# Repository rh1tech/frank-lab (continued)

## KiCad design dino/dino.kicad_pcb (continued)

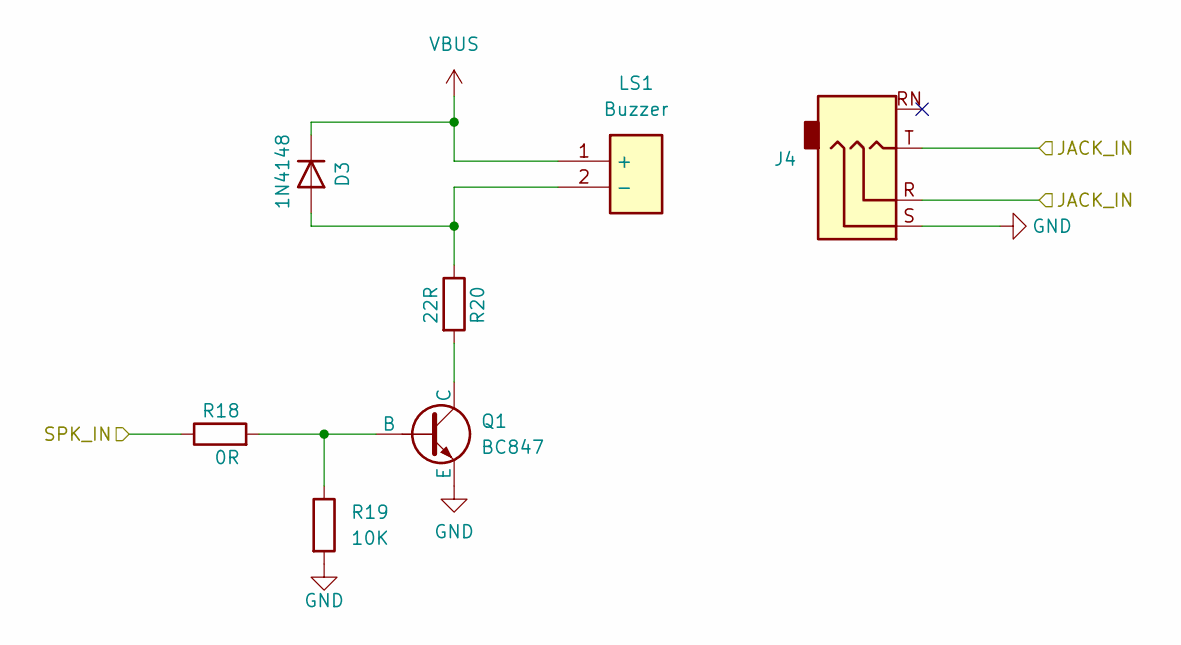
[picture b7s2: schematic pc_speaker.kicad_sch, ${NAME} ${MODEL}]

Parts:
D3: 1N4148; D_SOD-323
J4: PJ-320D; AudioJack_3.5mm_PJ320D_AudioOut
LS1: Buzzer; Buzzer_12x8.5RM6.5; Mouser Part Number 490-CMT-7525-80SMTTR
Q1: BC847; SOT-23
R18: 0R; R_0603_1608Metric
R19: 10K; R_0603_1608Metric
R20: 22R; R_0603_1608Metric

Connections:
/JACK_IN: J4.R, J4.T; also elsewhere on the board
/SPK_IN: R18.1; also elsewhere on the board
GND: J4.S, Q1.3 (E), R19.2; also elsewhere on the board
unnamed: D3.2 (A), LS1.2 (-), R20.1
unnamed: Q1.2 (B), R18.2, R19.1
unnamed: Q1.1 (C), R20.2
VBUS: D3.1 (K), LS1.1 (+); also elsewhere on the board

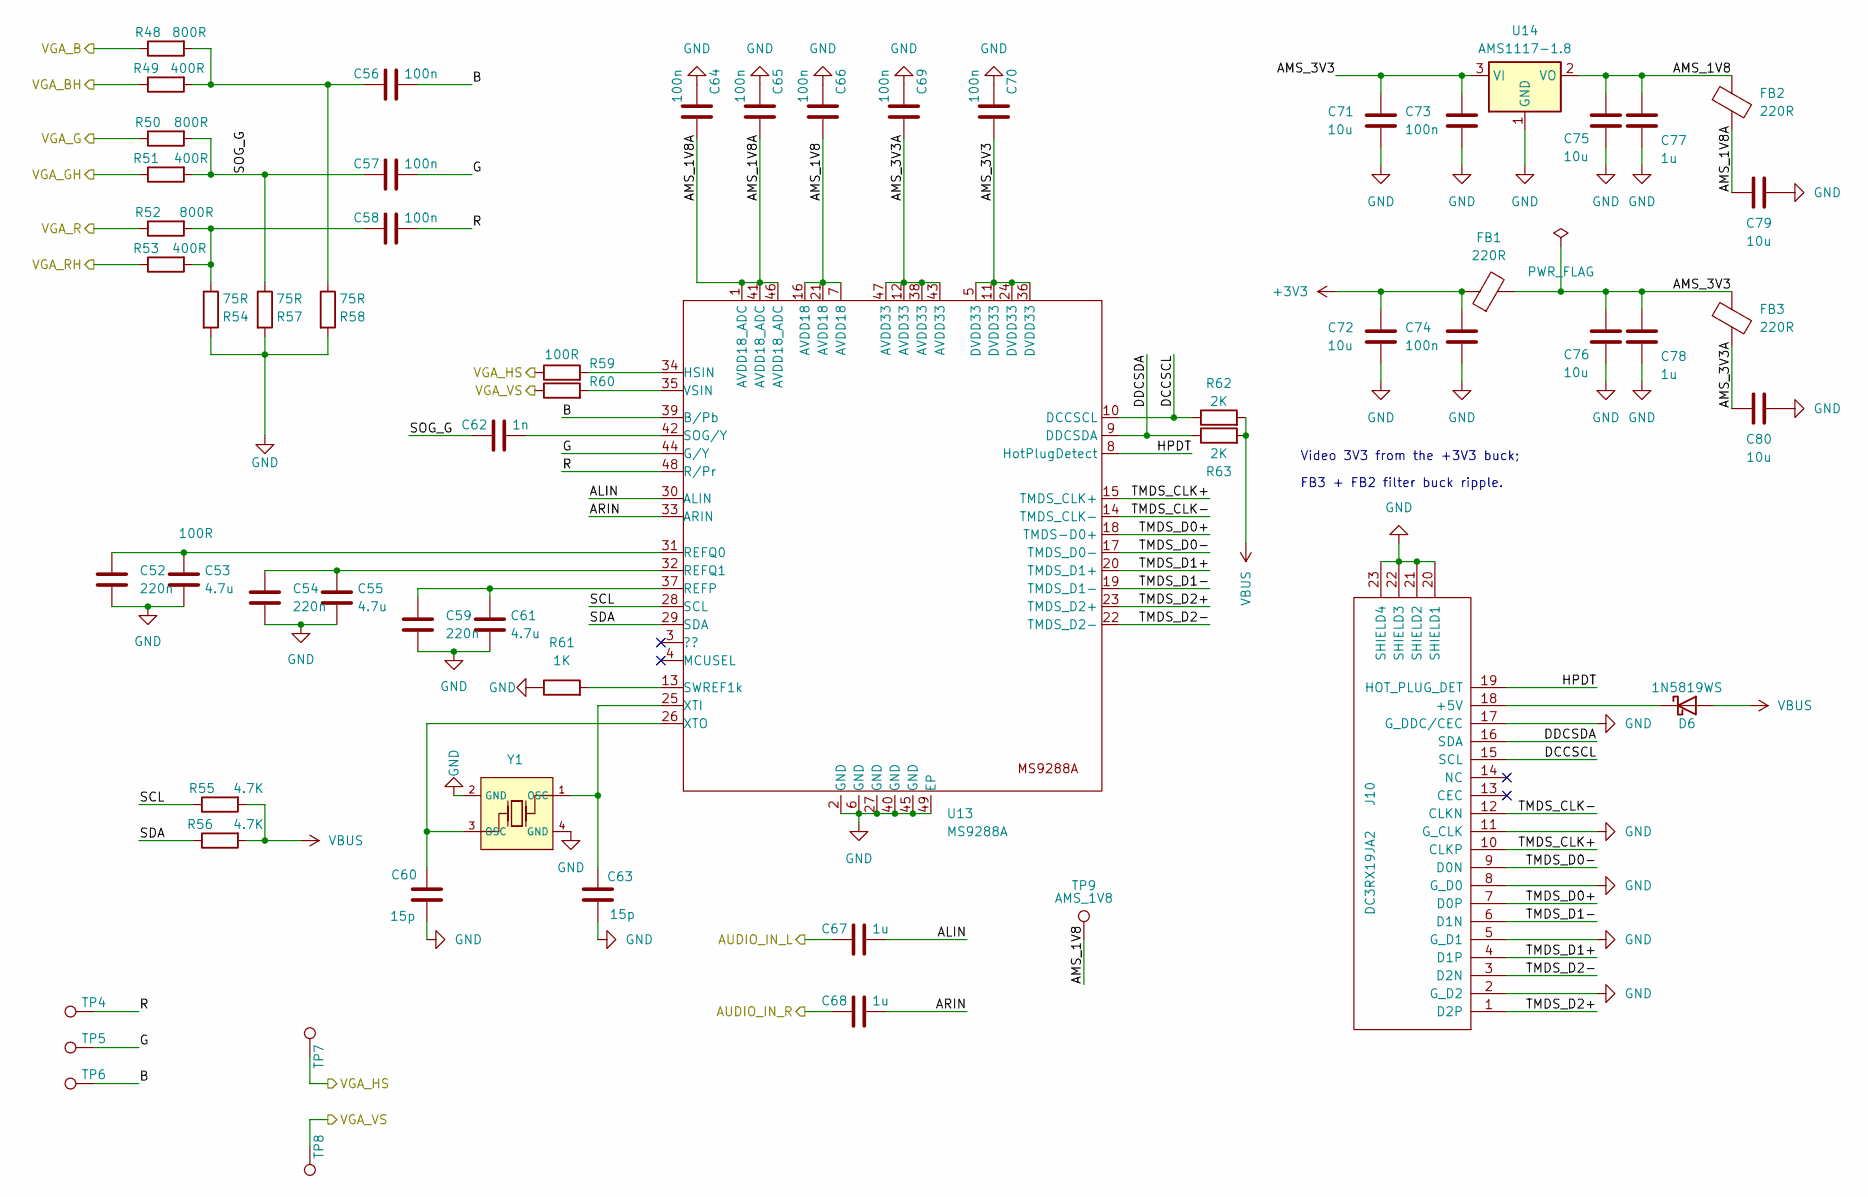
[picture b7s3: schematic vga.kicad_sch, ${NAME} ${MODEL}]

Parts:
C52, C54, C59: 220n; C_0603_1608Metric
C53, C55, C61: 4.7u; C_0603_1608Metric
C56, C57, C58, C64, C65, C66, C69, C70, C73, C74: 100n; C_0603_1608Metric
C60, C63: 15p; C_0603_1608Metric
C62: 1n; C_0603_1608Metric
C67, C68, C77, C78: 1u; C_0603_1608Metric
C71, C72, C75, C76, C79, C80: 10u; C_0603_1608Metric
D6: 1N5819WS; D_SOD-323
FB1, FB2, FB3: 220R; L_0805_2012Metric
J10: DC3RX19JA2; HDMI_Female
R48, R50, R52: 800R; R_0603_1608Metric
R49, R51, R53: 400R; R_0603_1608Metric
R54, R57, R58: 75R; R_0603_1608Metric
R55, R56: 4.7K; R_0603_1608Metric
R59, R60: 100R; R_0603_1608Metric
R61: 1K; R_0603_1608Metric
R62, R63: 2K; R_0603_1608Metric
TP4: R; TestPoint_Pad_1.0x1.0mm
TP5: G; TestPoint_Pad_1.0x1.0mm
TP6: B; TestPoint_Pad_1.0x1.0mm
TP7: HS; TestPoint_Pad_1.0x1.0mm
TP8: VS; TestPoint_Pad_1.0x1.0mm
TP9: AMS_1V8; TestPoint_Pad_1.0x1.0mm
U13: MS9288A; QFN-48_7x7mm_P0.4mm
U14: AMS1117-1.8; SOT-223-3_TabPin2
Y1: 24.576 MHz; Crystal_SMD_2520-4Pin; Frequency Tolerance ±10ppm; Part X322512MSB4SI

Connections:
+3V3: C72.1, C74.1, FB1.1; also elsewhere on the board
/HDMI_AUDIO: C67.2, C68.2; also elsewhere on the board
/RP2350B/GP30: R48.1; also elsewhere on the board
/RP2350B/GP31: R49.1; also elsewhere on the board
/RP2350B/GP32: R50.1; also elsewhere on the board
/RP2350B/GP33: R51.1; also elsewhere on the board
/RP2350B/GP34: R52.1; also elsewhere on the board
/RP2350B/GP35: R53.1; also elsewhere on the board
/RP2350B/GP36: R59.1, TP7.1 (1_1); also elsewhere on the board
/RP2350B/GP37: R60.1, TP8.1 (1_1); also elsewhere on the board
/Video/ALIN: C67.1, U13.30 (ALIN)
/Video/AMS_1V8: C66.1, C75.1, C77.1, FB2.1, TP9.1 (1_1), U13.7 (AVDD18), U13.16 (AVDD18), U13.21 (AVDD18), U14.2 (VO)
/Video/AMS_1V8A: C64.1, C65.1, C79.1, FB2.2, U13.1 (AVDD18_ADC), U13.41 (AVDD18_ADC), U13.46 (AVDD18_ADC)
/Video/AMS_3V3: C70.1, C71.1, C73.1, C76.1, C78.1, FB1.2, FB3.1, U13.5 (DVDD33), U13.11 (DVDD33), U13.24 (DVDD33), U13.36 (DVDD33), U14.3 (VI)
/Video/AMS_3V3A: C69.1, C80.1, FB3.2, U13.12 (AVDD33), U13.38 (AVDD33), U13.43 (AVDD33), U13.47 (AVDD33)
/Video/ARIN: C68.1, U13.33 (ARIN)
/Video/B: C56.1, TP6.1 (1_1), U13.39 (B/Pb)
/Video/DCCSCL: J10.15 (SCL), R62.1, U13.10 (DCCSCL)
/Video/DDCSDA: J10.16 (SDA), R63.1, U13.9 (DDCSDA)
/Video/G: C57.1, TP5.1 (1_1), U13.44 (G/Y)
/Video/HPDT: J10.19 (HOT_PLUG_DET), U13.8 (HotPlugDetect)
/Video/R: C58.1, TP4.1 (1_1), U13.48 (R/Pr)
/Video/SCL: R55.1, U13.28 (SCL)
/Video/SDA: R56.1, U13.29 (SDA)
/Video/SOG_G: C57.2, C62.2, R50.2, R51.2, R57.1
/Video/TMDS_CLK+: J10.10 (CLKP), U13.15 (TMDS_CLK+)
/Video/TMDS_CLK-: J10.12 (CLKN), U13.14 (TMDS_CLK-)
/Video/TMDS_D0+: J10.7 (D0P), U13.18 (TMDS-D0+)
/Video/TMDS_D0-: J10.9 (D0N), U13.17 (TMDS_D0-)
/Video/TMDS_D1+: J10.4 (D1P), U13.20 (TMDS_D1+)
/Video/TMDS_D1-: J10.6 (D1N), U13.19 (TMDS_D1-)
/Video/TMDS_D2+: J10.1 (D2P), U13.23 (TMDS_D2+)
/Video/TMDS_D2-: J10.3 (D2N), U13.22 (TMDS_D2-)
GND: C52.2, C53.2, C54.2, C55.2, C59.2, C60.2, C61.2, C63.2, C64.2, C65.2, C66.2, C69.2, C70.2, C71.2, C72.2, C73.2, C74.2, C75.2, C76.2, C77.2, C78.2, C79.2, C80.2, J10.2 (G_D2), J10.5 (G_D1), J10.8 (G_D0), J10.11 (G_CLK), J10.17 (G_DDC/CEC), J10.20 (SHIELD1), J10.21 (SHIELD2), J10.22 (SHIELD3), J10.23 (SHIELD4), R54.2, R57.2, R58.2, R61.1, U13.2 (GND), U13.6 (GND), U13.27 (GND), U13.40 (GND), U13.45 (GND), U13.49 (EP), U14.1 (GND), Y1.2 (GND), Y1.4 (GND); also elsewhere on the board
unnamed: C56.2, R48.2, R49.2, R58.1
unnamed: C58.2, R52.2, R53.2, R54.1
unnamed: D6.1 (K), J10.18 (+5V)
unnamed: R59.2, U13.34 (HSIN)
unnamed: C59.1, C61.1, U13.37 (REFP)
unnamed: C52.1, C53.1, U13.31 (REFQ0)
unnamed: C54.1, C55.1, U13.32 (REFQ1)
unnamed: C62.1, U13.42 (SOG/Y)
unnamed: R61.2, U13.13 (SWREF1k)
unnamed: R60.2, U13.35 (VSIN)
unnamed: C63.1, U13.25 (XTI), Y1.1 (OSC)
unnamed: C60.1, U13.26 (XTO), Y1.3 (OSC)
VBUS: D6.2 (A), R55.2, R56.2, R62.2, R63.2; also elsewhere on the board

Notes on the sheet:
FB3 + FB2 filter buck ripple.
Video 3V3 from the +3V3 buck;

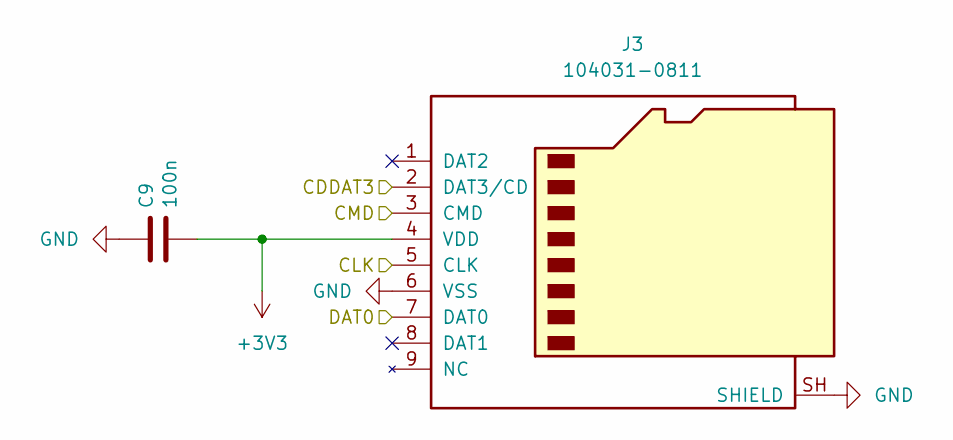
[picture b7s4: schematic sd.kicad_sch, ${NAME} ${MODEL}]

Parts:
C9: 100n; C_0603_1608Metric
J3: 104031-0811; MicroSD_SMD_Long

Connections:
+3V3: C9.2, J3.4 (VDD); also elsewhere on the board
/Micro SD/CDDAT3: J3.2 (DAT3/CD); also elsewhere on the board
/Micro SD/CLK: J3.5 (CLK); also elsewhere on the board
/Micro SD/CMD: J3.3 (CMD); also elsewhere on the board
/Micro SD/DAT0: J3.7 (DAT0); also elsewhere on the board
GND: C9.1, J3.6 (VSS), J3.SH (SHIELD); also elsewhere on the board

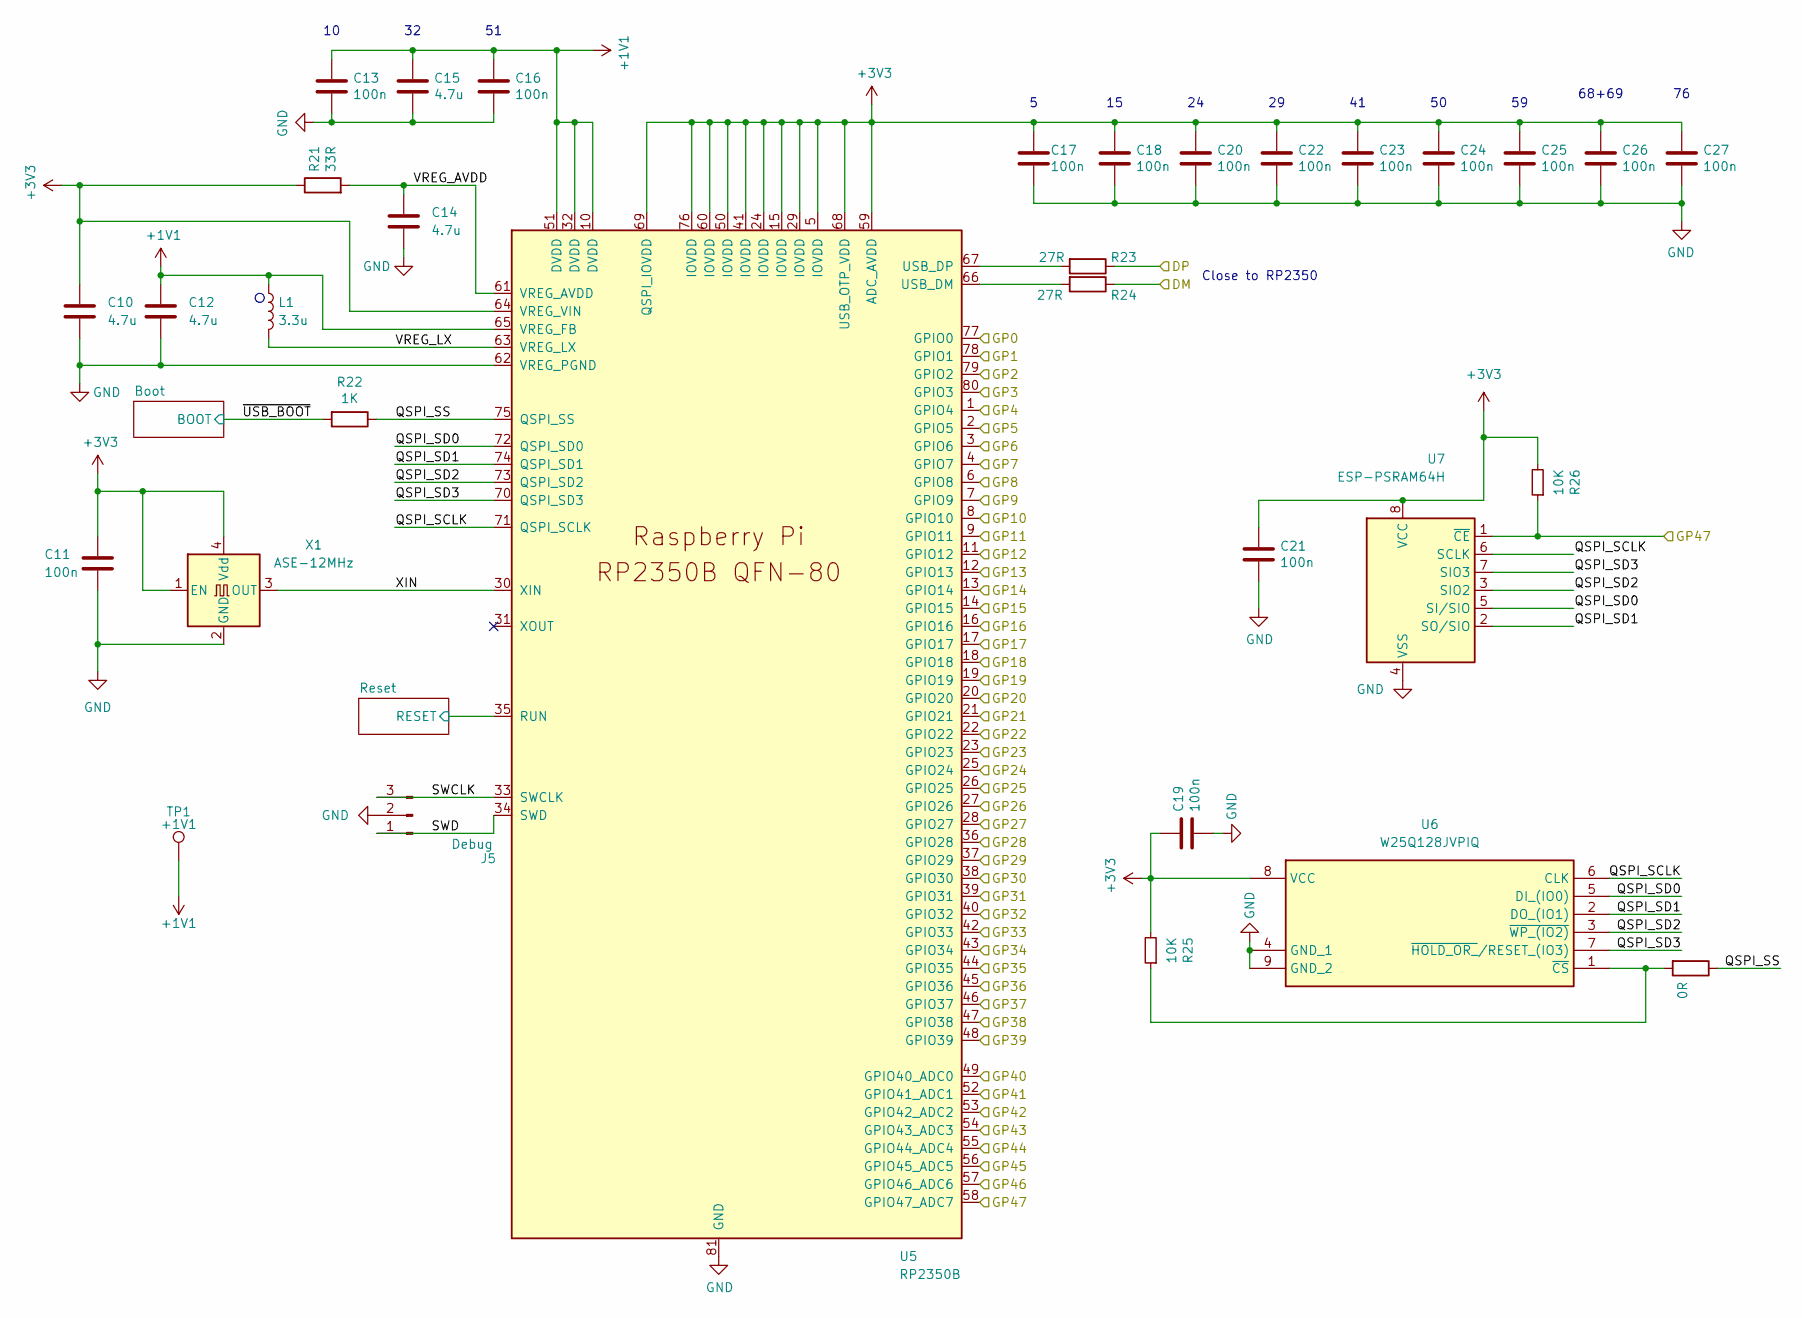
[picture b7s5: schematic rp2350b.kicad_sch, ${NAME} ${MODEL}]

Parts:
C10, C12, C14, C15: 4.7u; C_0603_1608Metric
C11, C13, C16, C17, C18, C19, C20, C21, C22, C23, C24, C25, C26, C27: 100n; C_0603_1608Metric
J5: Debug; JST_SH_1x03_P1.00mm_Vertical
L1: 3.3u; L_LQH2MCN100K02L
R21: 33R; R_0603_1608Metric
R22: 1K; R_0603_1608Metric
R23, R24: 27R; R_0603_1608Metric
R25, R26: 10K; R_0603_1608Metric
R27: 0R; R_0603_1608Metric
TP1: +1V1; TestPoint_Pad_1.0x1.0mm
U5: RP2350B; RP2350-QFN-80_10x10_P0.4mm
U6: W25Q128JVPIQ; SON127P600X500X80-9N-D; Mouser Part Number 454-W25Q128JVPIQ
U7: ESP-PSRAM64H; SO-8
X1: ASE-12MHz; Oscillator_SMD_3225_4Pin

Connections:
+1V1: C12.1, C13.1, C15.1, C16.1, L1.1, TP1.1 (1_1), U5.10 (DVDD), U5.32 (DVDD), U5.51 (DVDD), U5.65 (VREG_FB)
+3V3: C10.1, C11.1, C17.1, C18.1, C19.1, C20.1, C21.1, C22.1, C23.1, C24.1, C25.1, C26.1, C27.1, R21.1, R25.2, R26.2, U5.5 (IOVDD), U5.15 (IOVDD), U5.24 (IOVDD), U5.29 (IOVDD), U5.41 (IOVDD), U5.50 (IOVDD), U5.59 (ADC_AVDD), U5.60 (IOVDD), U5.64 (VREG_VIN), U5.68 (USB_OTP_VDD), U5.69 (QSPI_IOVDD), U5.76 (IOVDD), U6.8 (VCC), U7.8 (VCC), X1.1 (EN), X1.4 (Vdd); also elsewhere on the board
/A0: U5.77 (GPIO0); also elsewhere on the board
/A1: U5.78 (GPIO1); also elsewhere on the board
/A2: U5.79 (GPIO2); also elsewhere on the board
/A3: U5.80 (GPIO3); also elsewhere on the board
/A4: U5.1 (GPIO4); also elsewhere on the board
/A5: U5.2 (GPIO5); also elsewhere on the board
/A6: U5.3 (GPIO6); also elsewhere on the board
/A7: U5.4 (GPIO7); also elsewhere on the board
/A8: U5.6 (GPIO8); also elsewhere on the board
/A9: U5.7 (GPIO9); also elsewhere on the board
/A10: U5.8 (GPIO10); also elsewhere on the board
/A11: U5.9 (GPIO11); also elsewhere on the board
/A12: U5.11 (GPIO12); also elsewhere on the board
/A13: U5.12 (GPIO13); also elsewhere on the board
/A14: U5.13 (GPIO14); also elsewhere on the board
/A15: U5.14 (GPIO15); also elsewhere on the board
/CLK: U5.36 (GPIO28); also elsewhere on the board
/D0: U5.16 (GPIO16); also elsewhere on the board
/D1: U5.17 (GPIO17); also elsewhere on the board
/D2: U5.18 (GPIO18); also elsewhere on the board
/D3: U5.19 (GPIO19); also elsewhere on the board
/D4: U5.20 (GPIO20); also elsewhere on the board
/D5: U5.21 (GPIO21); also elsewhere on the board
/D6: U5.22 (GPIO22); also elsewhere on the board
/D7: U5.23 (GPIO23); also elsewhere on the board
/INT: U5.47 (GPIO38); also elsewhere on the board
/M1: U5.28 (GPIO27); also elsewhere on the board
/MREQ: U5.25 (GPIO24); also elsewhere on the board
/Micro SD/CDDAT3: U5.52 (GPIO41_ADC1); also elsewhere on the board
/Micro SD/CLK: U5.53 (GPIO42_ADC2); also elsewhere on the board
/Micro SD/CMD: U5.54 (GPIO43_ADC3); also elsewhere on the board
/Micro SD/DAT0: U5.49 (GPIO40_ADC0); also elsewhere on the board
/NMI: U5.48 (GPIO39); also elsewhere on the board
/RD: U5.26 (GPIO25); also elsewhere on the board
/RESET: U5.37 (GPIO29); also elsewhere on the board
/RP2350B/DM: R24.1; also elsewhere on the board
/RP2350B/DP: R23.1; also elsewhere on the board
/RP2350B/GP30: U5.38 (GPIO30); also elsewhere on the board
/RP2350B/GP31: U5.39 (GPIO31); also elsewhere on the board
/RP2350B/GP32: U5.40 (GPIO32); also elsewhere on the board
/RP2350B/GP33: U5.42 (GPIO33); also elsewhere on the board
/RP2350B/GP34: U5.43 (GPIO34); also elsewhere on the board
/RP2350B/GP35: U5.44 (GPIO35); also elsewhere on the board
/RP2350B/GP36: U5.45 (GPIO36); also elsewhere on the board
/RP2350B/GP37: U5.46 (GPIO37); also elsewhere on the board
/RP2350B/GP47: R26.1, U5.58 (GPIO47_ADC7), U7.1 (~CE)
/RP2350B/QSPI_SCLK: U5.71 (QSPI_SCLK), U6.6 (CLK), U7.6 (SCLK)
/RP2350B/QSPI_SD0: U5.72 (QSPI_SD0), U6.5 (DI_(IO0)), U7.5 (SI/SIO)
/RP2350B/QSPI_SD1: U5.74 (QSPI_SD1), U6.2 (DO_(IO1)), U7.2 (SO/SIO)
/RP2350B/QSPI_SD2: U5.73 (QSPI_SD2), U6.3 (~WP_(IO2)), U7.3 (SIO2)
/RP2350B/QSPI_SD3: U5.70 (QSPI_SD3), U6.7 (~HOLD_OR_/RESET_(IO3)), U7.7 (SIO3)
/RP2350B/QSPI_SS: R22.1, R27.1, U5.75 (QSPI_SS)
/RP2350B/Reset/RESET: U5.35 (RUN); also elsewhere on the board
/RP2350B/SWCLK: J5.3, U5.33 (SWCLK)
/RP2350B/SWD: J5.1, U5.34 (SWD)
/RP2350B/VREG_AVDD: C14.1, R21.2, U5.61 (VREG_AVDD)
/RP2350B/VREG_LX: L1.2, U5.63 (VREG_LX)
/RP2350B/XIN: U5.30 (XIN), X1.3 (OUT)
/RP2350B/~USB_BOOT: R22.2; also elsewhere on the board
/SPEAKER: U5.57 (GPIO46_ADC6); also elsewhere on the board
/TAPE_UART_RX: U5.56 (GPIO45_ADC5); also elsewhere on the board
/UART0_TX: U5.55 (GPIO44_ADC4); also elsewhere on the board
/WR: U5.27 (GPIO26); also elsewhere on the board
GND: C10.2, C11.2, C12.2, C13.2, C14.2, C15.2, C16.2, C17.2, C18.2, C19.2, C20.2, C21.2, C22.2, C23.2, C24.2, C25.2, C26.2, C27.2, J5.2, U5.62 (VREG_PGND), U5.81 (GND), U6.4 (GND_1), U6.9 (GND_2), U7.4 (VSS), X1.2 (GND); also elsewhere on the board
unnamed: R24.2, U5.66 (USB_DM)
unnamed: R23.2, U5.67 (USB_DP)
unnamed: R25.1, R27.2, U6.1 (~CS)

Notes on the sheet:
Close to RP2350
68+69

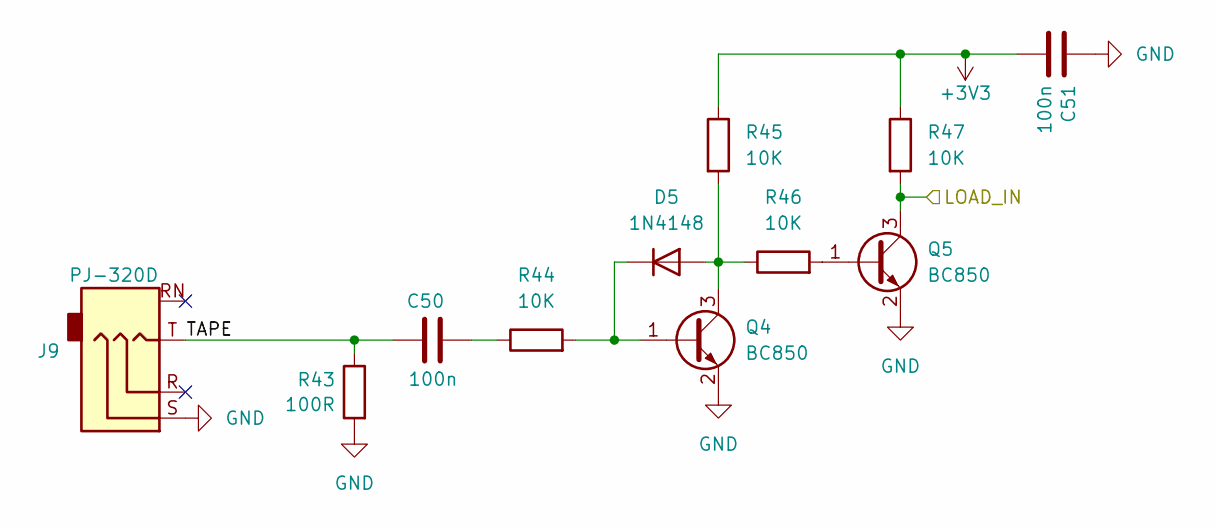
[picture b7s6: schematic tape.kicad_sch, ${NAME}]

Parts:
C50, C51: 100n; C_0603_1608Metric; LCSC C14663
D5: 1N4148; D_SOD-323; LCSC C2128
J9: PJ-320D; AudioJack_3.5mm_PJ320D_TapeIn; LCSC C431535
Q4, Q5: BC850; SOT-23; LCSC C503377
R43: 100R; R_0603_1608Metric; LCSC C22775
R44, R45, R46: 10K; R_0603_1608Metric; LCSC C2906982
R47: 10K; R_0603_1608Metric; LCSC C21190

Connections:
+3V3: C51.2, R45.1, R47.1; also elsewhere on the board
/TAPE_UART_RX: Q5.3 (C), R47.2; also elsewhere on the board
/Tape/TAPE: C50.1, J9.T, R43.1
GND: C51.1, J9.S, Q4.2 (E), Q5.2 (E), R43.2; also elsewhere on the board
unnamed: C50.2, R44.1
unnamed: D5.2 (A), Q4.3 (C), R45.2, R46.1
unnamed: D5.1 (K), Q4.1 (B), R44.2
unnamed: Q5.1 (B), R46.2

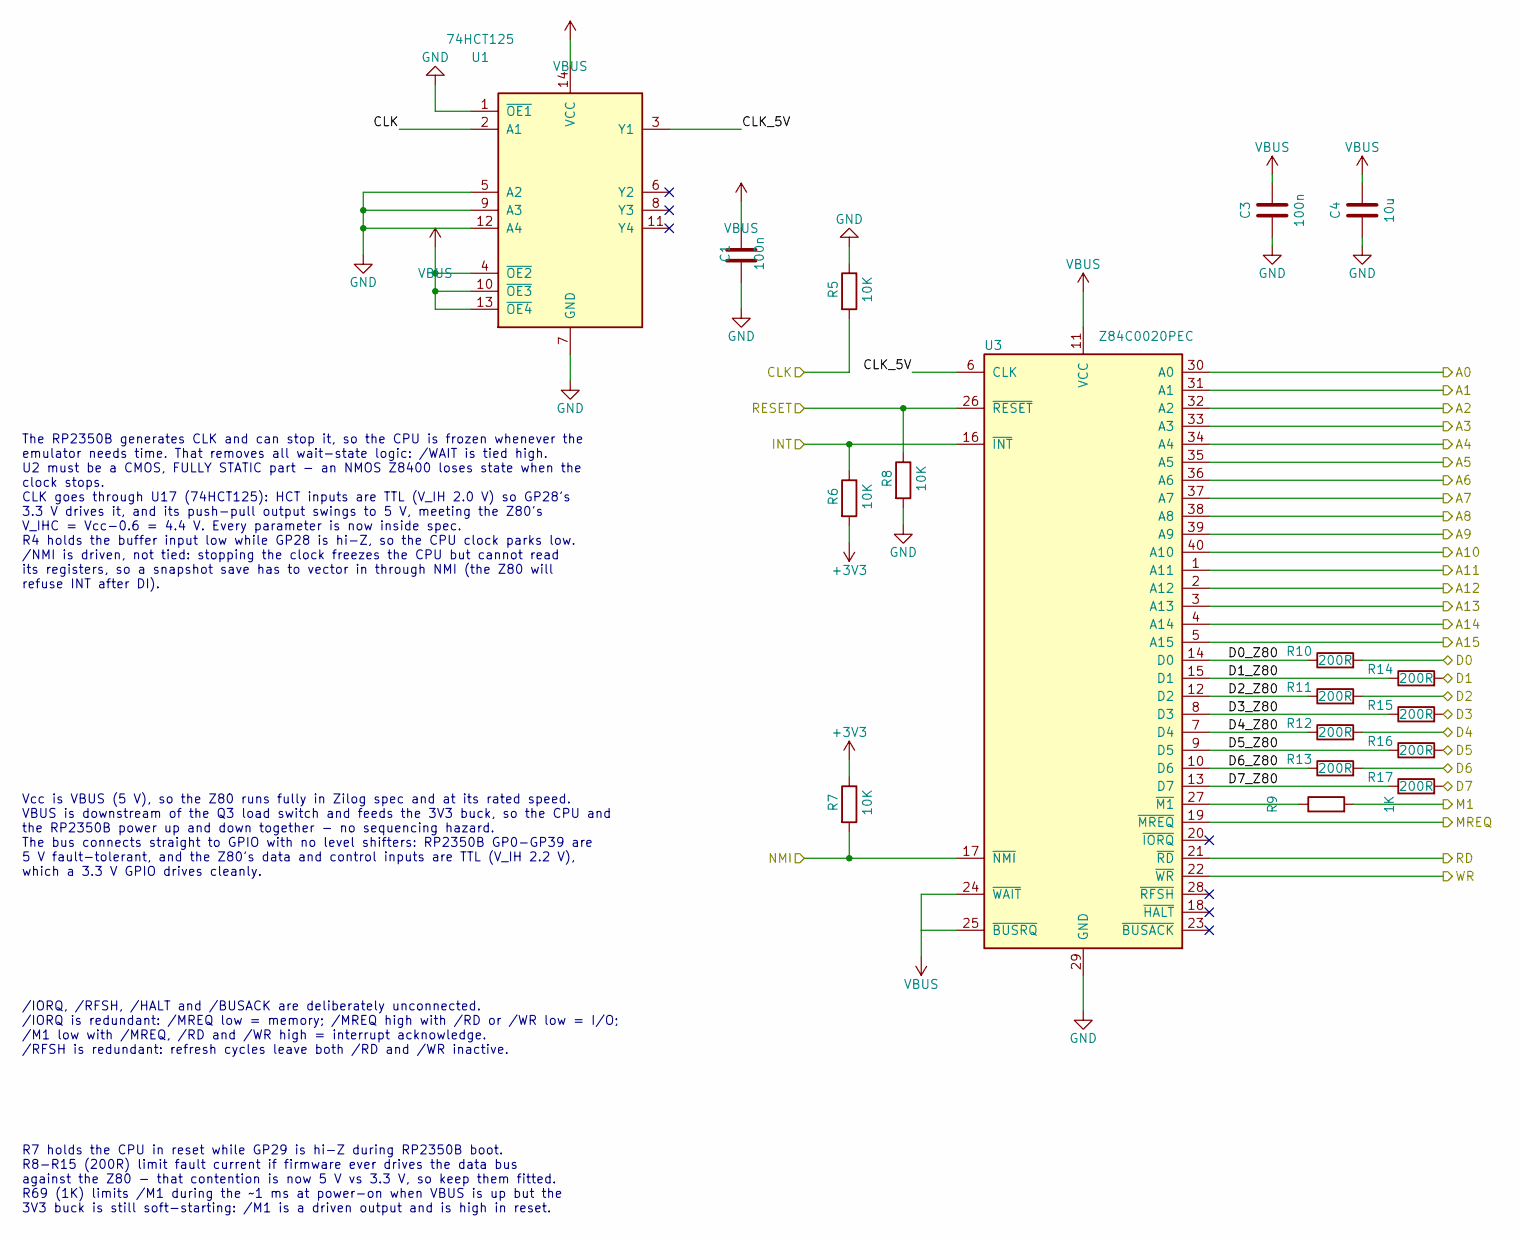
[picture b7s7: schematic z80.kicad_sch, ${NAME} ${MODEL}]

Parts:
C1, C3: 100n; C_0603_1608Metric
C4: 10u; C_0603_1608Metric
R5, R6, R7, R8: 10K; R_0603_1608Metric
R9: 1K; R_0603_1608Metric
R10, R11, R12, R13, R14, R15, R16, R17: 200R; R_0603_1608Metric
U1: 74HCT125; SOIC127P600X175-14N
U3: Z84C0020PEC; DIP-40_W15.24mm_Socket

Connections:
+3V3: R6.2, R7.1; also elsewhere on the board
/A0: U3.30 (A0); also elsewhere on the board
/A1: U3.31 (A1); also elsewhere on the board
/A2: U3.32 (A2); also elsewhere on the board
/A3: U3.33 (A3); also elsewhere on the board
/A4: U3.34 (A4); also elsewhere on the board
/A5: U3.35 (A5); also elsewhere on the board
/A6: U3.36 (A6); also elsewhere on the board
/A7: U3.37 (A7); also elsewhere on the board
/A8: U3.38 (A8); also elsewhere on the board
/A9: U3.39 (A9); also elsewhere on the board
/A10: U3.40 (A10); also elsewhere on the board
/A11: U3.1 (A11); also elsewhere on the board
/A12: U3.2 (A12); also elsewhere on the board
/A13: U3.3 (A13); also elsewhere on the board
/A14: U3.4 (A14); also elsewhere on the board
/A15: U3.5 (A15); also elsewhere on the board
/CLK: R5.2, U1.2 (A1); also elsewhere on the board
/D0: R10.2; also elsewhere on the board
/D1: R14.2; also elsewhere on the board
/D2: R11.2; also elsewhere on the board
/D3: R15.2; also elsewhere on the board
/D4: R12.2; also elsewhere on the board
/D5: R16.2; also elsewhere on the board
/D6: R13.2; also elsewhere on the board
/D7: R17.2; also elsewhere on the board
/INT: R6.1, U3.16 (~INT); also elsewhere on the board
/M1: R9.2; also elsewhere on the board
/MREQ: U3.19 (~MREQ); also elsewhere on the board
/NMI: R7.2, U3.17 (~NMI); also elsewhere on the board
/RD: U3.21 (~RD); also elsewhere on the board
/RESET: R8.1, U3.26 (~RESET); also elsewhere on the board
/WR: U3.22 (~WR); also elsewhere on the board
/Z80/CLK_5V: U1.3 (Y1), U3.6 (CLK)
/Z80/D0_Z80: R10.1, U3.14 (D0)
/Z80/D1_Z80: R14.1, U3.15 (D1)
/Z80/D2_Z80: R11.1, U3.12 (D2)
/Z80/D3_Z80: R15.1, U3.8 (D3)
/Z80/D4_Z80: R12.1, U3.7 (D4)
/Z80/D5_Z80: R16.1, U3.9 (D5)
/Z80/D6_Z80: R13.1, U3.10 (D6)
/Z80/D7_Z80: R17.1, U3.13 (D7)
GND: C1.2, C3.2, C4.2, R5.1, R8.2, U1.1 (~OE1), U1.5 (A2), U1.7 (GND), U1.9 (A3), U1.12 (A4), U3.29 (GND); also elsewhere on the board
unnamed: R9.1, U3.27 (~M1)
VBUS: C1.1, C3.1, C4.1, U1.4 (~OE2), U1.10 (~OE3), U1.13 (~OE4), U1.14 (VCC), U3.11 (VCC), U3.24 (~WAIT), U3.25 (~BUSRQ); also elsewhere on the board

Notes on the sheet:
/IORQ, /RFSH, /HALT and /BUSACK are deliberately unconnected. /IORQ is redundant: /MREQ low = memory; /MREQ high with /RD or /WR low = I/O; /M1 low with /MREQ, /RD and /WR high = interrupt acknowledge. /RFSH is redundant: refresh cycles leave both /RD and /WR inactive.
Vcc is VBUS (5 V), so the Z80 runs fully in Zilog spec and at its rated speed. VBUS is downstream of the Q3 load switch and feeds the 3V3 buck, so the CPU and the RP2350B power up and down together - no sequencing hazard. The bus connects straight to GPIO with no level shifters: RP2350B GP0-GP39 ar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
R7 holds the CPU in reset while GP29 is hi-Z during RP2350B boot. R8-R15 (200R) limit fault current if firmware ever drives the data bus against the Z80 - that contention is now 5 V vs 3.3 V, so keep them fitted. R69 (1K) limits /M1 during the ~1 ms at power-on when VBUS is up but the 3V3 buck is s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
The RP2350B generates CLK and can stop it, so the CPU is frozen whenever the emulator needs time. That removes all wait-state logic: /WAIT is tied high. U2 must be a CMOS, FULLY STATIC part - an NMOS Z8400 loses state when the clock stops. CLK goes through U17 (74HCT125): HCT inputs are TTL (V_IH 2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

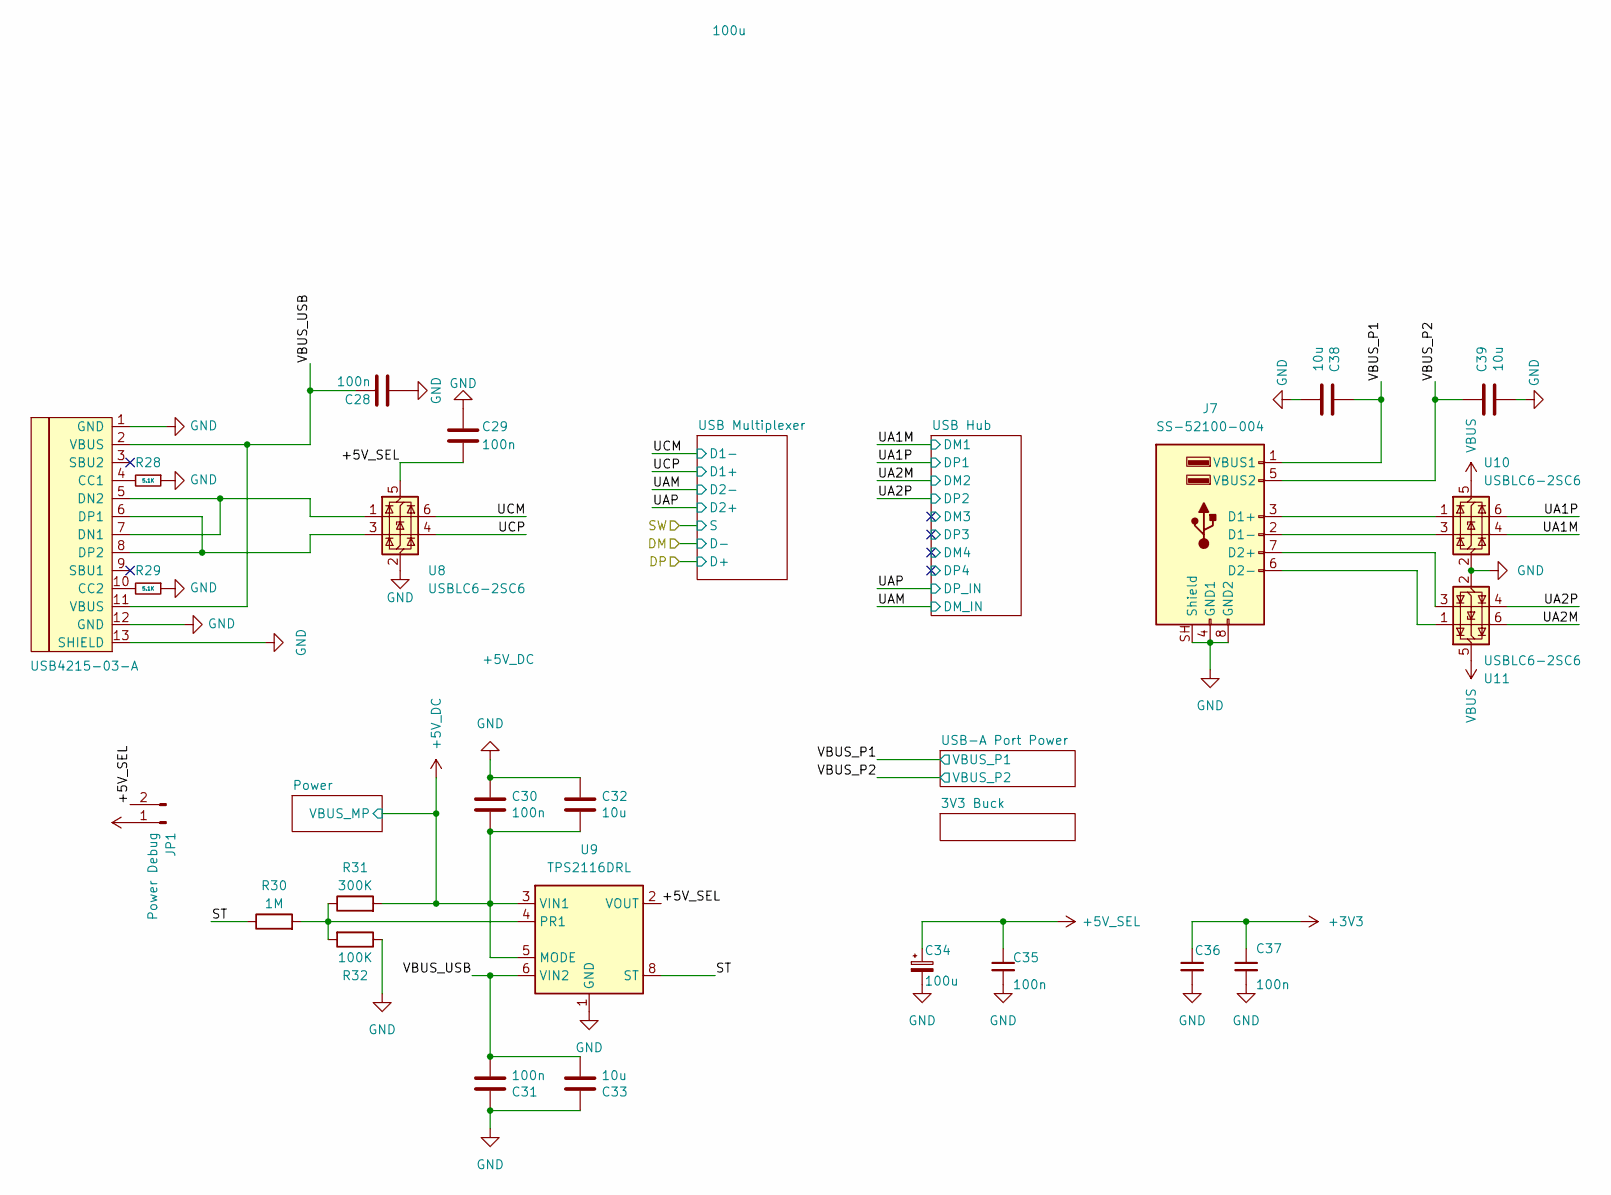
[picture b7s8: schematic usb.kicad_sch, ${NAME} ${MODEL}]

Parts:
C28, C29, C30, C31, C35, C37: 100n; C_0603_1608Metric
C32, C33, C38, C39: 10u; C_0603_1608Metric
C34: 100u; CP_Radial_D6.3mm_P2.50mm
C36: 100u; C_1206_3216Metric
J6: USB4215-03-A; USB_C_Receptacle; LCSC C165948
J7: SS-52100-004; USB_A_Stacked
JP1: Power Debug; SolderJumper-2_P1.3mm_Open_Pad1.0x1.5mm
R28, R29: 5.1K; R_0603_1608Metric
R30: 1M; R_0603_1608Metric
R31: 300K; R_0603_1608Metric
R32: 100K; R_0603_1608Metric
U8, U10, U11: USBLC6-2SC6; SOT-23-6
U9: TPS2116DRL; SOT-583-8

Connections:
+3V3: C36.1, C37.1; also elsewhere on the board
+5V_DC: C30.2, C32.2, JP1.1, R31.2, U9.3 (VIN1), U9.5 (MODE); also elsewhere on the board
+5V_SEL: C29.2, C34.1, C35.1, JP1.2, U8.5 (VBUS), U9.2 (VOUT), U9.7 (VOUT); also elsewhere on the board
/USB, Power/ST: R30.1, U9.8 (ST)
/USB, Power/UA1M: U10.4 (I/O2); also elsewhere on the board
/USB, Power/UA1P: U10.6 (I/O1); also elsewhere on the board
/USB, Power/UA2M: U11.6 (I/O1); also elsewhere on the board
/USB, Power/UA2P: U11.4 (I/O2); also elsewhere on the board
/USB, Power/UCM: U8.6 (I/O1); also elsewhere on the board
/USB, Power/UCP: U8.4 (I/O2); also elsewhere on the board
/USB, Power/VBUS_P1: C38.1, J7.1 (VBUS1); also elsewhere on the board
/USB, Power/VBUS_P2: C39.1, J7.5 (VBUS2); also elsewhere on the board
/USB, Power/VBUS_USB: C28.1, C31.2, C33.2, J6.2 (VBUS), J6.11 (VBUS), U9.6 (VIN2)
GND: C28.2, C29.1, C30.1, C31.1, C32.1, C33.1, C34.2, C35.2, C36.2, C37.2, C38.2, C39.2, J6.1 (GND), J6.12 (GND), J6.13 (SHIELD), J7.4 (GND1), J7.8 (GND2), J7.SH (Shield), R28.1, R29.1, R32.1, U8.2 (GND), U9.1 (GND), U10.2 (GND), U11.2 (GND); also elsewhere on the board
unnamed: J6.4 (CC1), R28.2
unnamed: J6.10 (CC2), R29.2
unnamed: J6.5 (DN2), J6.7 (DN1), U8.1 (I/O1)
unnamed: J6.6 (DP1), J6.8 (DP2), U8.3 (I/O2)
unnamed: J7.3 (D1+), U10.1 (I/O1)
unnamed: J7.2 (D1-), U10.3 (I/O2)
unnamed: J7.7 (D2+), U11.3 (I/O2)
unnamed: J7.6 (D2-), U11.1 (I/O1)
unnamed: R30.2, R31.1, R32.2, U9.4 (PR1)
VBUS: U10.5 (VBUS), U11.5 (VBUS); also elsewhere on the board

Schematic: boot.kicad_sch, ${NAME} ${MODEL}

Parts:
S3: Boot; Button_SMD_3x4x2mm; Mouser Part Number 611-KMR221G-LFS

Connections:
/RP2350B/~USB_BOOT: S3.2, S3.4; also elsewhere on the board
GND: S3.1, S3.3; also elsewhere on the board

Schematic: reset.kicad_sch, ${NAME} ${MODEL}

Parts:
C40: 1n; C_0603_1608Metric
S4: Reset; Button_SMD_3x4x2mm; Mouser Part Number 611-KMR221G-LFS

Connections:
/RP2350B/Reset/RESET: C40.2, S4.2, S4.4; also elsewhere on the board
GND: C40.1, S4.1, S4.3; also elsewhere on the board

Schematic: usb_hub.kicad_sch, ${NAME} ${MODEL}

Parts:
C5: 1u; C_0603_1608Metric
C6: 4.7u; C_0603_1608Metric; LCSC C1746
C7, C8: 100n; C_0603_1608Metric
U4: MW7211A; SOIC127P600X175-16N

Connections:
/USB, Power/UA1M: U4.7 (DM3); also elsewhere on the board
/USB, Power/UA1P: U4.8 (DP3); also elsewhere on the board
/USB, Power/UA2M: U4.5 (DM2); also elsewhere on the board
/USB, Power/UA2P: U4.6 (DP2); also elsewhere on the board
/USB, Power/UAM: U4.10 (DMU); also elsewhere on the board
/USB, Power/UAP: U4.11 (DPU); also elsewhere on the board
/USB, Power/USB Hub/DM3: U4.3 (DM1)
/USB, Power/USB Hub/DM4: U4.1 (DM0)
/USB, Power/USB Hub/DP3: U4.4 (DP1)
/USB, Power/USB Hub/DP4: U4.2 (DP0)
/USB, Power/USB Hub/VD33: C5.1, C7.1, U4.12 (VD33), U4.14 (VD3)
GND: C5.2, C6.2, C7.2, C8.2, U4.15 (GND), U4.16 (GND); also elsewhere on the board
VBUS: C6.1, C8.1, U4.13 (VDD5); also elsewhere on the board

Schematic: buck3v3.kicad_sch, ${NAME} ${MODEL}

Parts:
C81, C82, C85: 10u; C_0603_1608Metric
C83, C86: 100n; C_0603_1608Metric
C84: 100u; C_1206_3216Metric
C87: 22p; C_0603_1608Metric
FB4: 330R 2A; L_0805_2012Metric
L3: 2.2uH; L_Cenker_CKCS3015
R64: 100K; R_0603_1608Metric
R65: 22K; R_0603_1608Metric
TP10: +5V_BUCK; TestPoint_Pad_1.0x1.0mm
TP11: LX; TestPoint_Pad_1.0x1.0mm
U15: SY8089AAAC; SOT-23-5

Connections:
+3V3: C84.1, C85.1, C86.1, C87.1, L3.2, R64.1; also elsewhere on the board
/USB, Power/3V3 Buck/+5V_BUCK: C81.1, C82.1, C83.1, FB4.2, TP10.1 (1_1), U15.1 (EN), U15.4 (IN)
/USB, Power/3V3 Buck/FB: C87.2, R64.2, R65.1, U15.5 (FB)
GND: C81.2, C82.2, C83.2, C84.2, C85.2, C86.2, R65.2, U15.2 (GND); also elsewhere on the board
unnamed: L3.1, TP11.1 (1_1), U15.3 (LX)
VBUS: FB4.1; also elsewhere on the board

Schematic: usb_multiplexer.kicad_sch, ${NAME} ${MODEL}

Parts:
C2: 100n; C_0603_1608Metric
R4: 10K; R_0603_1608Metric
U2: TS3USB221RSER; Texas_R-PUQFN-N10

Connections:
+3V3: C2.2, R4.1, U2.10 (VCC); also elsewhere on the board
/RP2350B/DM: U2.7 (D-); also elsewhere on the board
/RP2350B/DP: U2.8 (D+); also elsewhere on the board
/USB, Power/SW: R4.2, U2.9 (S); also elsewhere on the board
/USB, Power/UAM: U2.4 (2D-); also elsewhere on the board
/USB, Power/UAP: U2.3 (2D+); also elsewhere on the board
/USB, Power/UCM: U2.2 (1D-); also elsewhere on the board
/USB, Power/UCP: U2.1 (1D+); also elsewhere on the board
GND: C2.1, U2.5 (GND), U2.6 (~OE); also elsewhere on the board

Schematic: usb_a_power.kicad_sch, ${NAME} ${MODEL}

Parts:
C88, C91: 100u; CP_Radial_D6.3mm_P2.50mm
C89, C90: 10u; C_0603_1608Metric
C92, C93: 100n; C_0603_1608Metric
D7: Red; LED_0805_2012Metric_Pad1.15x1.40mm_HandSolder
R66, R67, R68: 100K; R_0603_1608Metric
R69: 1K; R_0603_1608Metric
U16, U17: CH217K; SOT-23-6

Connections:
/USB, Power/USB-A Port Power/USB_OC: D7.1 (K), R68.2, U16.3 (FLAG#), U17.3 (FLAG#)
/USB, Power/VBUS_P1: C93.1, U16.1 (VOUT); also elsewhere on the board
/USB, Power/VBUS_P2: C92.1, U17.1 (VOUT); also elsewhere on the board
GND: C88.2, C89.2, C90.2, C91.2, C92.2, C93.2, R66.2, R67.2, U16.2 (GND), U16.4 (EN#), U17.2 (GND), U17.4 (EN#); also elsewhere on the board
unnamed: D7.2 (A), R69.2
unnamed: R66.1, U16.5 (ISET)
unnamed: R67.1, U17.5 (ISET)
VBUS: C88.1, C89.1, C90.1, C91.1, R68.1, R69.1, U16.6 (VIN), U17.6 (VIN); also elsewhere on the board
